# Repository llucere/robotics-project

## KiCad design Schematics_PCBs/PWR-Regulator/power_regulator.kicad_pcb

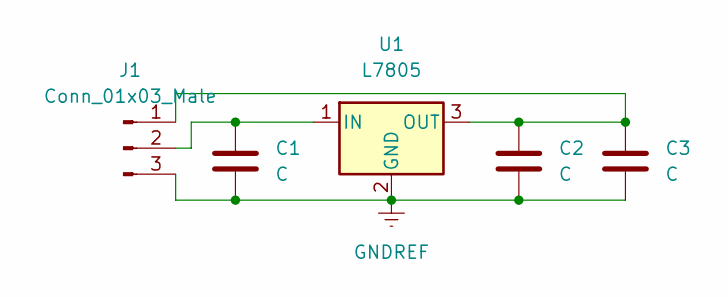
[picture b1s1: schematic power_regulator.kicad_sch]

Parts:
C1, C2, C3: C; CP_Radial_D5.0mm_P2.50mm
J1: Conn_01x03_Male; PinHeader_1x03_P2.54mm_Vertical
U1: L7805; SOT-23

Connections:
GNDREF: C1.2, C2.2, C3.2, J1.3, U1.2 (GND)
unnamed: C1.1, J1.2, U1.1 (IN)
unnamed: C2.1, C3.1, J1.1, U1.3 (OUT)

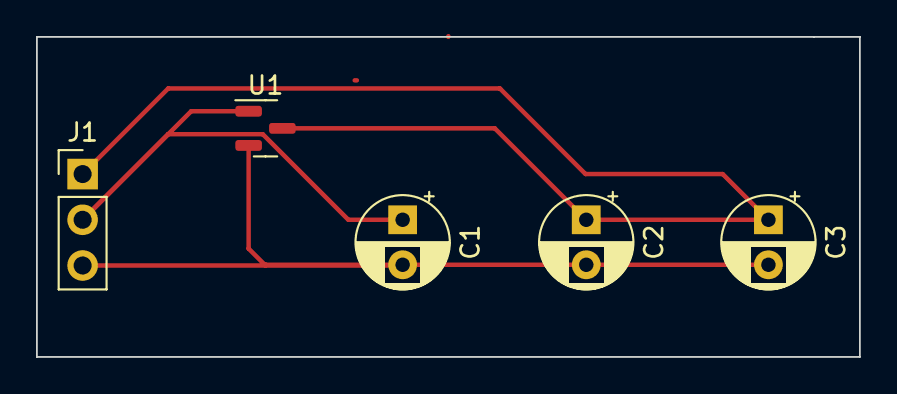
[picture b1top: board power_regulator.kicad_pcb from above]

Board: 2 copper layers, 45.7 x 17.8 mm, 5 parts (0 on the bottom side), 3 nets.

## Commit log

2022-12-14 Repost
    reposting the github
2022-12-14 Minor Changes
    slightly improved optimization, commented out unnecessary stuff, converted micros to millis for now (until solution is made for preventing micros from wrapping after around an hour)
2022-12-14 documenting, changing stuff
2023-01-23 removed redundancy
    speed > 0 always
2023-01-26 idk wha ti did
